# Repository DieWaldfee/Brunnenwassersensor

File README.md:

# Brunnenwassersensor
to measure groundwater level and temperature

Der Brunnenwassersensor sitzt in einem KG-Rohr DN50 (Abwasserrohr) und misst per Laser die Wasserhöhe, die Wassertemperatur und die Lufttemperatur im Brunnenschacht. Die Konstruktion ist für ein 3.5m langes Brunnenrohr ausgelegt, sodass die normale Grundwasseränderung (Sommer/Winter) wie auch die dynamische Grundwasserabsenkung im Brunnen bei Betrieb einer Brunnenpumpe erfasst werden kann. Übertragen werden die Messdaten via MQTT an einen MQTT-Broker. So kann der Messwert in einer Hausautomation erfasst und dargestellt werden.

Wozu braucht man das: keine Ahnung, aber es geht :-)
Scherz beiseite: Messung der dynamischen Wasserabsenkung bei Einsatz einer Brunnenpumpe, Messung des saisonalen Grundwasserspiegels und dessen Temperatur.

Aufgebaut ist die Elektronik mit einem ESP32, zwei DS18B20 Temperatursensoren und einem Waveshare TOF Laser Sensor B. Der Lasersensor ist besonders, da er eine Laserfokussierung von 1-2° hat - ideal, um im dünnen KG-Rohr DN50 zu messen!
Hier der Link zum Sensor-Datasheet: https://www.waveshare.com/wiki/TOF_Laser_Range_Sensor_(B)
Um den Sensor korrekt zu zentrieren nehmt ihr euer Handy mit dessen Kamera. Die CCDs sehen den Laser - das Auge kann den Laser nicht direkt sehen. => Linse mittig am Ende des Rohres positionieren / halten. Sensor in seiner Halterung ausrichten - fertig.

Im Repository liegen die STL-Dateien, um die Komponenten mit einem 3D-Drucker auszudrucken, der C++-Code für den ESP32, das Eagle-file für das Platinendesign auf Lochrasterkarte (zum Nachlöten) und die Fusiom360-Dateien.

Einrichtung:
Einstellung für euer eingesetzten DS18B20-Sensoren - die haben natürlich andere Adressen...

Offset-Einstellung zwischen Oberkante Sensor und Oberkante Gelände (GOK):

...und danach natürlich eure User/Passwörter in der secrets.h:<p>

viel Spaß beim Nachbauen :-)

### Abhängigkeiten:
OneWire.h:_____________OneWire by Jim Studt, Tom Pollard, Robin James... v2.3.8 (über Arduino IDE)<br>
DallasTemperature.h:___DallasTemperature by Miles Burton v4.0.3 (über Arduino IDE)<br>
WiFi.h:________________Arduino IDE<br>
WiFiClient.h:__________Arduino IDE<br>
PubSubClient.h:________PubSubClient by Nick O'Leary v2.8 (über Arduino IDE) [also tested with PubSubClient3 V3.2.1]<br>
Wire.h:________________by Jim Studt, Tom Pollard, Robiun James... v2.3.8 (über Arduino IDE)<br>
esp_task_wdt.h:________Espressif IDE<br>

### verwendete IDE
Im Verzeichnis `ESP23_Dev_Kit_V4` liegen die Arduino-files. Im Verzeichnis `vscode` liegt der gleiche Inhalt für VSCode. Zukünftig wird im VSCode weiter entwickelt. Wenn die Parallelität zu aufwändig wird nehme ich die Arduino IDE aus dem Repository. Solange das *.ino-file im Repository liegt wird es auch aktuell gehalten.

### Board ESP32
esp32 by Espressif Systems v1.0.6 (über Arduino IDE)<br>
Getestet habe ich auch v2.0.5<br>

Ausgabe im serial Monitor unter debug=1:

so sieht das bei mir im ioBroker (...oder wo auch immer ihr das weiterverwenden wollt :-)) aus:

Hier die Platine:

Aufbau des Sonsorrohrs:

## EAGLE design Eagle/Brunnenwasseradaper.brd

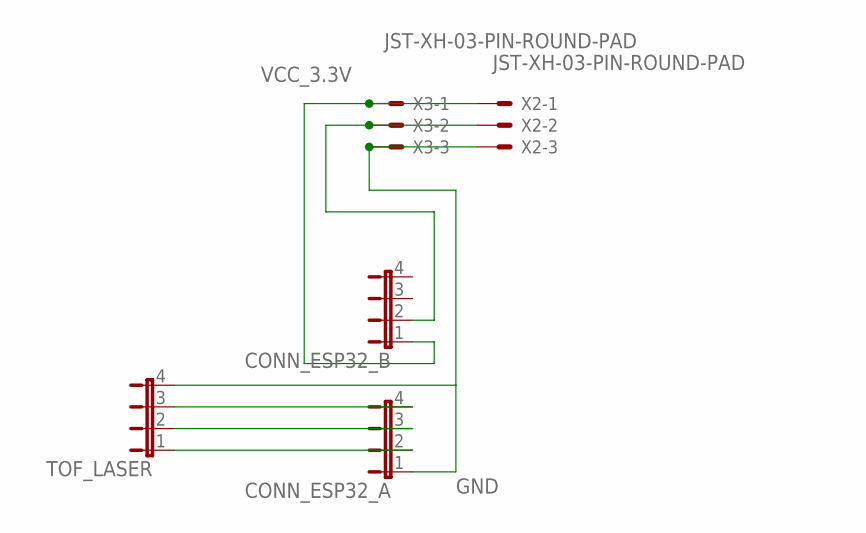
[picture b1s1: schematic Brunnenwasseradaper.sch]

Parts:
CONN_ESP32_A, CONN_ESP32_B: JP4E; JP4
TOF_LASER: JP4E; JP4
X2, X3: JST-XH-03-PIN-ROUND-PAD; JST-XH-03-PACKAGE-ROUND-PAD

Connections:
GND: CONN_ESP32_A.1, TOF_LASER.4, X2.3, X3.3
unnamed: CONN_ESP32_A.3, TOF_LASER.2
unnamed: CONN_ESP32_A.4, TOF_LASER.3
unnamed: CONN_ESP32_A.2, TOF_LASER.1
unnamed: CONN_ESP32_B.2, X2.2, X3.2
VCC_3.3V: CONN_ESP32_B.1, X2.1, X3.1

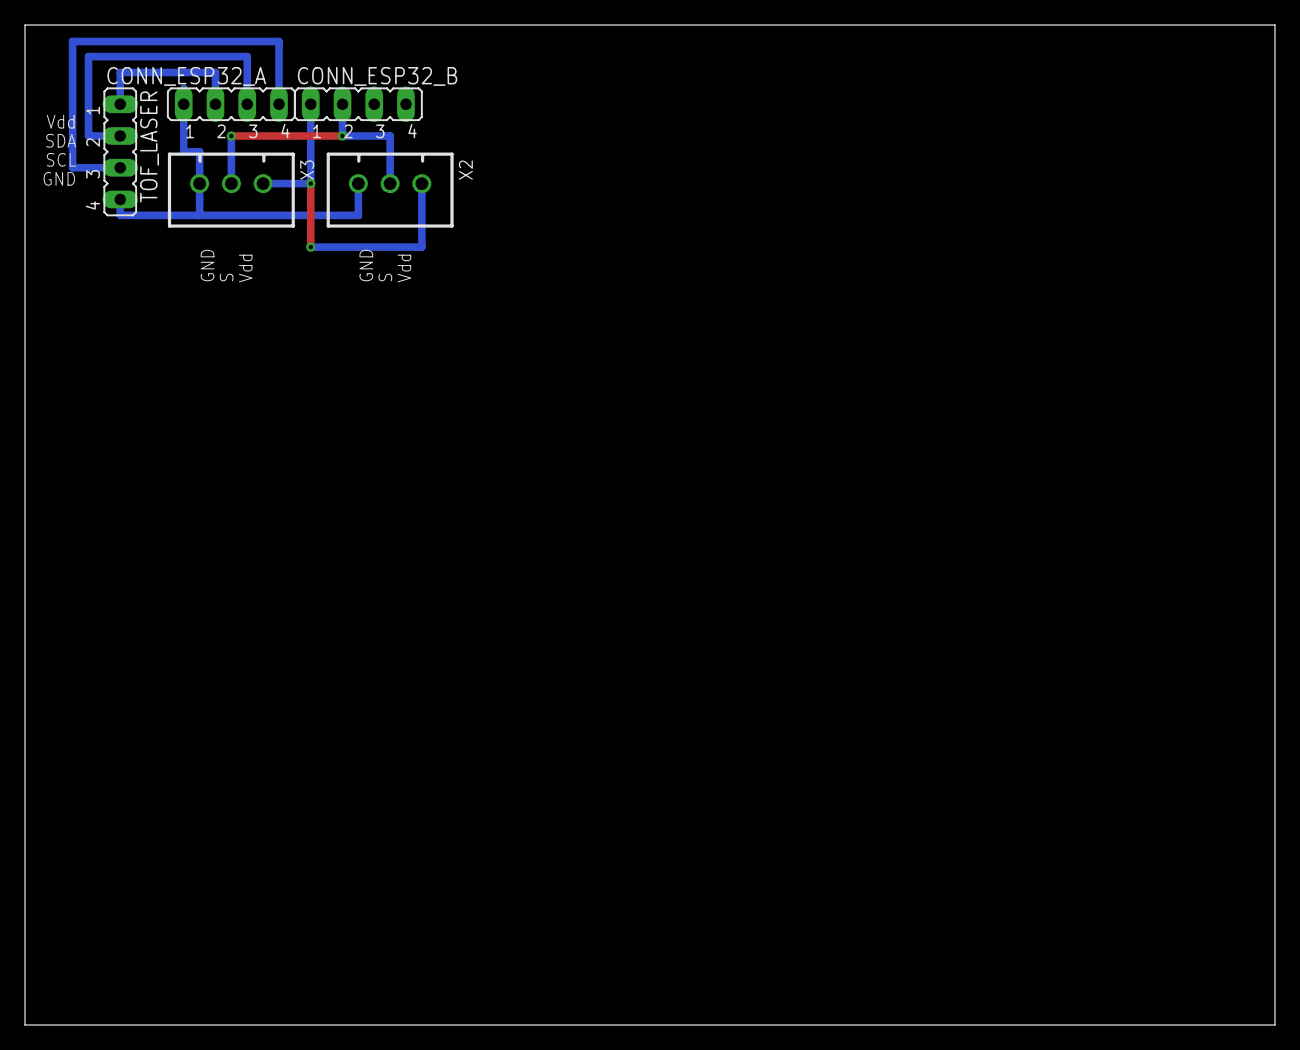
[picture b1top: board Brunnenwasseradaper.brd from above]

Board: 2 copper layers, 100.0 x 80.0 mm, 5 parts (0 on the bottom side), 6 nets.

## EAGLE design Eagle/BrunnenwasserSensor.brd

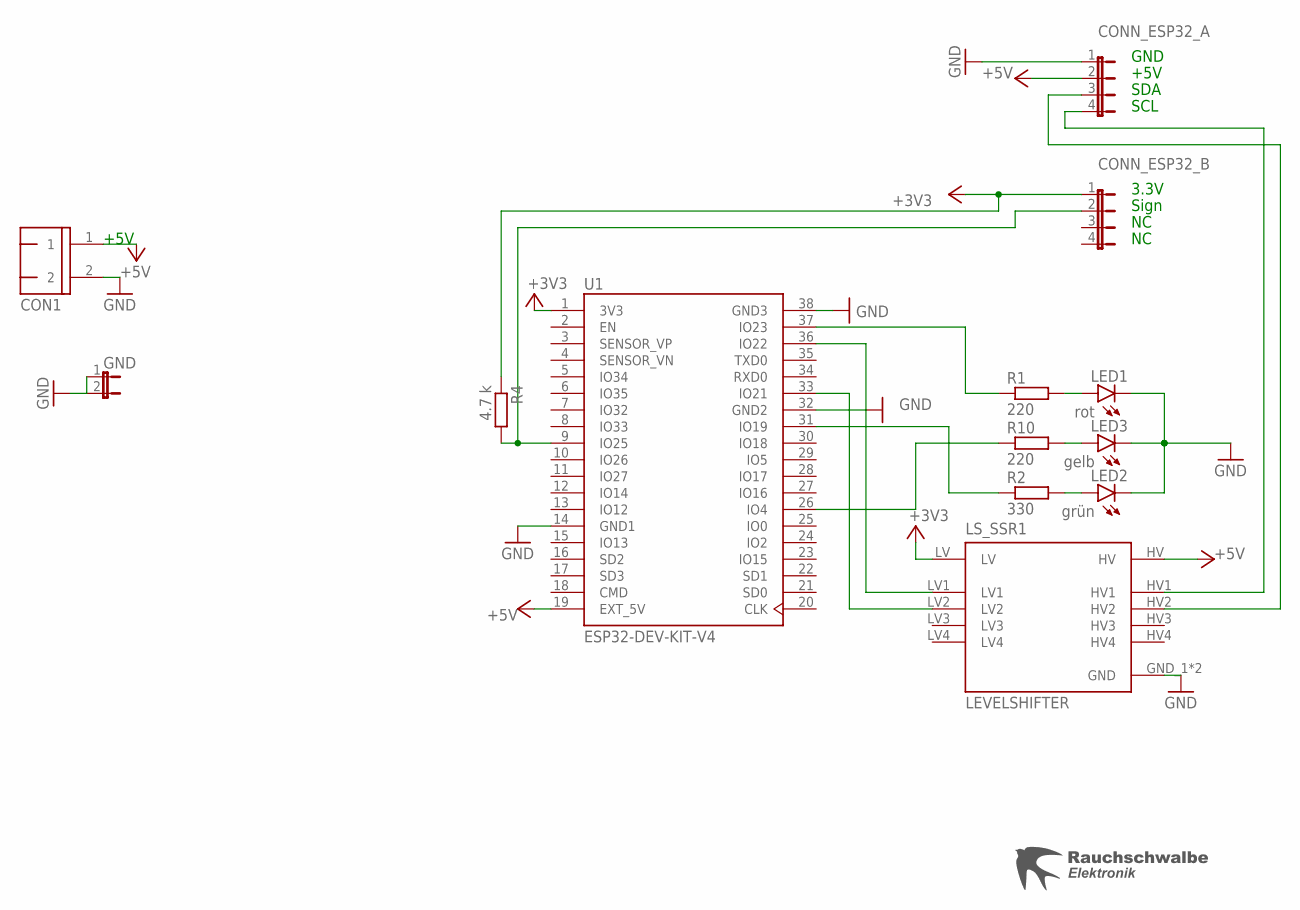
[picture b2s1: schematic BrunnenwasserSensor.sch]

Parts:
CON1: WAGO-500-2
CONN_ESP32_A, CONN_ESP32_B: JP4E; JP4
GND: JP1E; JP1
LED1: rot; LED3MM
LED2: grün; LED3MM
LED3: gelb; LED3MM
LS_SSR1: LEVELSHIFTER
R1, R10: 220; 0207/10
R2: 330; 0207/10
R4: 4.7 k; 0207/10
U1: ESP32-DEV-KIT-V4
U$1: LOGO_RAUCHSCHWALBE

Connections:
+3V3: CONN_ESP32_B.1, LS_SSR1.LV, R4.1, U1.1 (3V3)
+5V: CON1.1, CONN_ESP32_A.2, LS_SSR1.HV, U1.19 (EXT_5V)
GND: CON1.2, CONN_ESP32_A.1, GND.1, GND.2, LED1.K (C), LED2.K (C), LED3.K (C), LS_SSR1.GND_1 (GND), LS_SSR1.GND_2 (GND), U1.14 (GND1), U1.32 (GND2), U1.38 (GND3)
unnamed: R1.1, U1.37 (IO23)
unnamed: LED3.A, R10.2
unnamed: R2.1, U1.31 (IO19)
unnamed: LED1.A, R1.2
unnamed: LED2.A, R2.2
unnamed: CONN_ESP32_B.2, R4.2, U1.9 (IO25)
unnamed: R10.1, U1.26 (IO4)
SCL: LS_SSR1.LV1, U1.36 (IO22)
SCL2: CONN_ESP32_A.4, LS_SSR1.HV1
SDA: LS_SSR1.LV2, U1.33 (IO21)
SDA2: CONN_ESP32_A.3, LS_SSR1.HV2

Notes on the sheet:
+5V
GND
SDA
SCL
3.3V
Sign

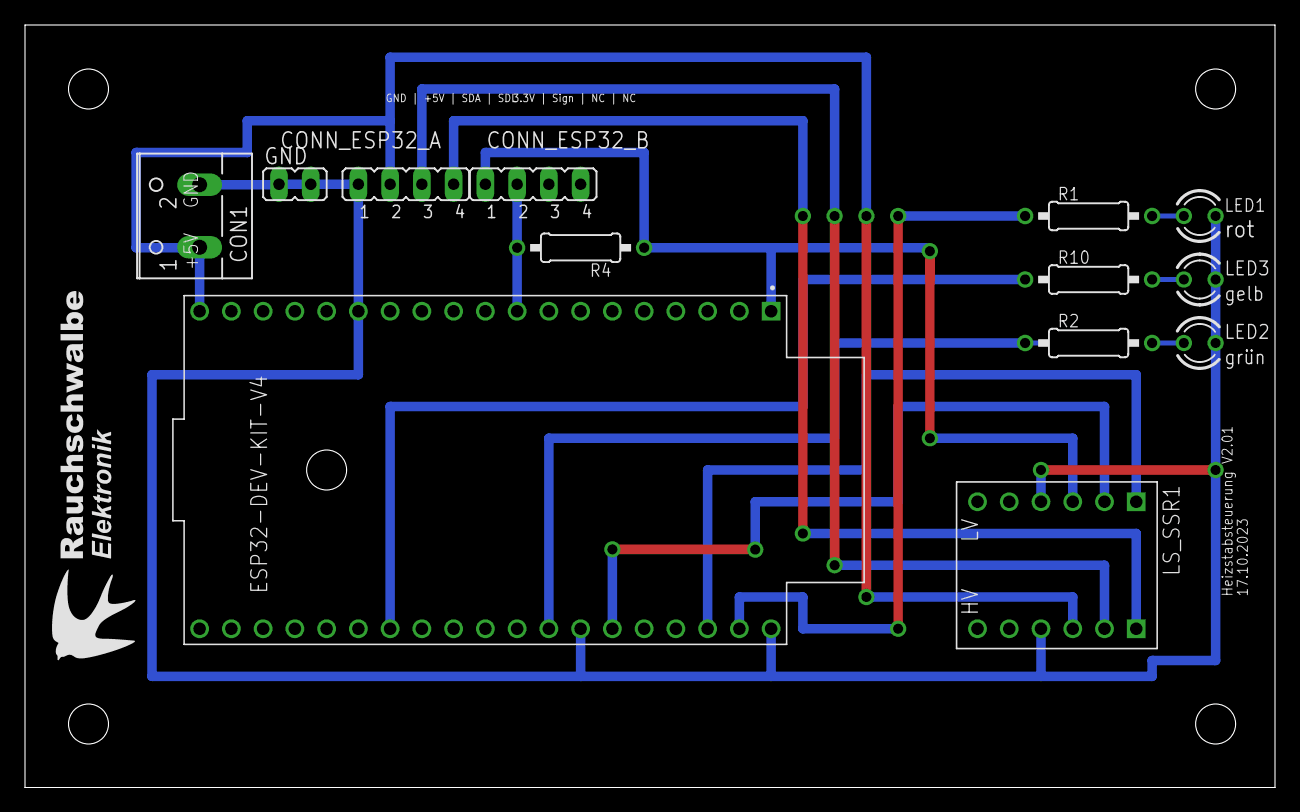
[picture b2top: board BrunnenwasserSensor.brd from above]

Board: 2 copper layers, 100.0 x 61.0 mm, 14 parts (0 on the bottom side), 14 nets.

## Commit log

2024-11-09 V0.9
2025-05-29 V1.1 IP- and MAC-Adress output in state
    V1.1 IP- and MAC-Adress output in state
2025-09-14 MQTT queued & safeReset umgesetzt
    - MQTT queued implemented
    - safeReset from "Heizstabsteuerung" integrated
    - Name mismatch in secrets.h solved
2026-01-07 reboot in boot sequence
    reboot in boot sequence, if TemSensor is not avaiable
2026-01-07 integrate vscode as alternitive IDE
2026-01-07 Update README with IDE usage details
    Added information about the IDE used for development and future plans regarding the Arduino IDE and VSCode.
2026-05-02 code robustness added
2026-05-02 VSCODE
